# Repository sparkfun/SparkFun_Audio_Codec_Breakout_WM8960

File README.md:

Stereo Audio Codec Breakout - WM8960
========================================

<table class="table table-hover table-striped table-bordered">
  <tr align="center">
   <td></td>
   <td></td>
  </tr>
  <tr align="center">
   <td><i>SparkFun Audio Codec Breakout - WM8960<br />[<a href="https://www.sparkfun.com/products/21250">BOB-21250</a>]</i></td>
   <td><i>SparkFun Audio Codec Breakout - WM8960 with Headers (Qwiic)<br />[<a href="https://www.sparkfun.com/products/21772">BOB-21772</a>]</i></td>
  </tr>
</table>

The SparkFun WM8960 Audio Codec Breakout is a low-power, high-quality stereo codec with 1W Stereo Class D speaker drivers and headphone drivers. The WM8960 acts as a stereo audio ADC and DAC and communicates using I<sup>2</sup>S, a standard audio data protocol (not to be confused with I<sup>2</sup>C). This audio codec is chock full of features some of which include advanced on-chip digital signal processing for automatic level control (ALC) for the line or microphone input, programmable gain amplifier (PGA), pop and click suppression, and its ability to configure I<sup>2</sup>S settings and analog audio path through software via I<sup>2</sup>C. 

The 6x flexible analog input pins allow for a variety of sound source signal types to be routed internally to the ADC inputs. These signal types include line level and microphone level (balanced, and un-balanced) sources. This allows you to accept audio from the sound card on your computer, headphone output of your smartphone, electret microphones, MEMs microphone, etc. The flexible analog signal routing includes PGAs and multiple boost stages so that it can accept a wide range of audio signal levels.

Its efficient class-D driver also means low heat and long battery life when driving 8&ohm; speakers at up to 1W per channel for portable audio applications. As an alternative output, users can also use the audio codec to drive 16&ohm; headphones at up to 40mW for portable audio applications.

Audio feeling a bit... empty? Turn on the 3D enhancement to artificially increase the separation between the left and right channels. In other words, you will feel as if the room is full of sound coming from all directions during playback.  We've written an extensive Arduino Library that allows you to easily control all of the audio codec's features from simple volume control to 3D-enhanced audio playback. 

The board breaks out the WM8960 pins along the edge of the PCB with 0.1"-spaced pins to connect to a breadboard. Utilizing our handy Qwiic system saves you from manually wiring the I<sup>2</sup>C port when configuring the audio codec's settings. A power LED (PWR) is included on the board to indicate when power is applied to the audio CODEC through 3.3V. It can be disabled by cutting the LED jumper on the bottom side. To power the analog (AVDD) and speaker driver (SPKVDD), you will need to include power on the VIN pin. The built-in XC6222 3.3V/700mA voltage regulator regulates the voltage down for the analog circuit. Jumpers for the analog circuit (i..e. AVDD-ISO) and speaker drivers (VIN/SPKVDD) are included for users that want to power each with a separate power supply. 

This board is great for projects that require you to encode or decode audio signals. Add the SparkFun Audio Codec Breakout WM8960 to your next portable digital player or immersive VR game. 

Repository Contents
-------------------

* **/Documents** - Datasheets, additional product information
* **/Hardware** - Eagle design files (.brd, .sch)

Documentation
--------------

* **[Library](https://github.com/sparkfun/SparkFun_WM8960_Arduino_Library)** - Arduino library for the Stereo Audio Codec Breakout - WM8960.
* **[SparkFun Fritzing Part](https://github.com/sparkfun/Fritzing_Parts/blob/main/products/21250_sfe_stereo_audio_codec_breakout_WM8960.fzpz)** - Fritzing diagrams for SparkFun products.
* **[Hookup Guide](https://learn.sparkfun.com/tutorials/2761)** - Basic hookup guide for the Stereo Audio Codec Breakout - WM8960.

Product Versions
----------------

* [BOB-21772](https://www.sparkfun.com/products/21772) - v1.0, with headers
* [BOB-21250](https://www.sparkfun.com/products/21250) - Initial Release, v1.0 

Version History
---------------
* v1.0 - Initial Release 

License Information
-------------------

This product is _**open source**_! 

Please review the LICENSE.md file for license information. 

If you have any questions or concerns on licensing, please contact technical support on our [SparkFun forums](https://forum.sparkfun.com/viewforum.php?f=152).

Distributed as-is; no warranty is given.

- Your friends at SparkFun.

_<COLLABORATION CREDIT>_

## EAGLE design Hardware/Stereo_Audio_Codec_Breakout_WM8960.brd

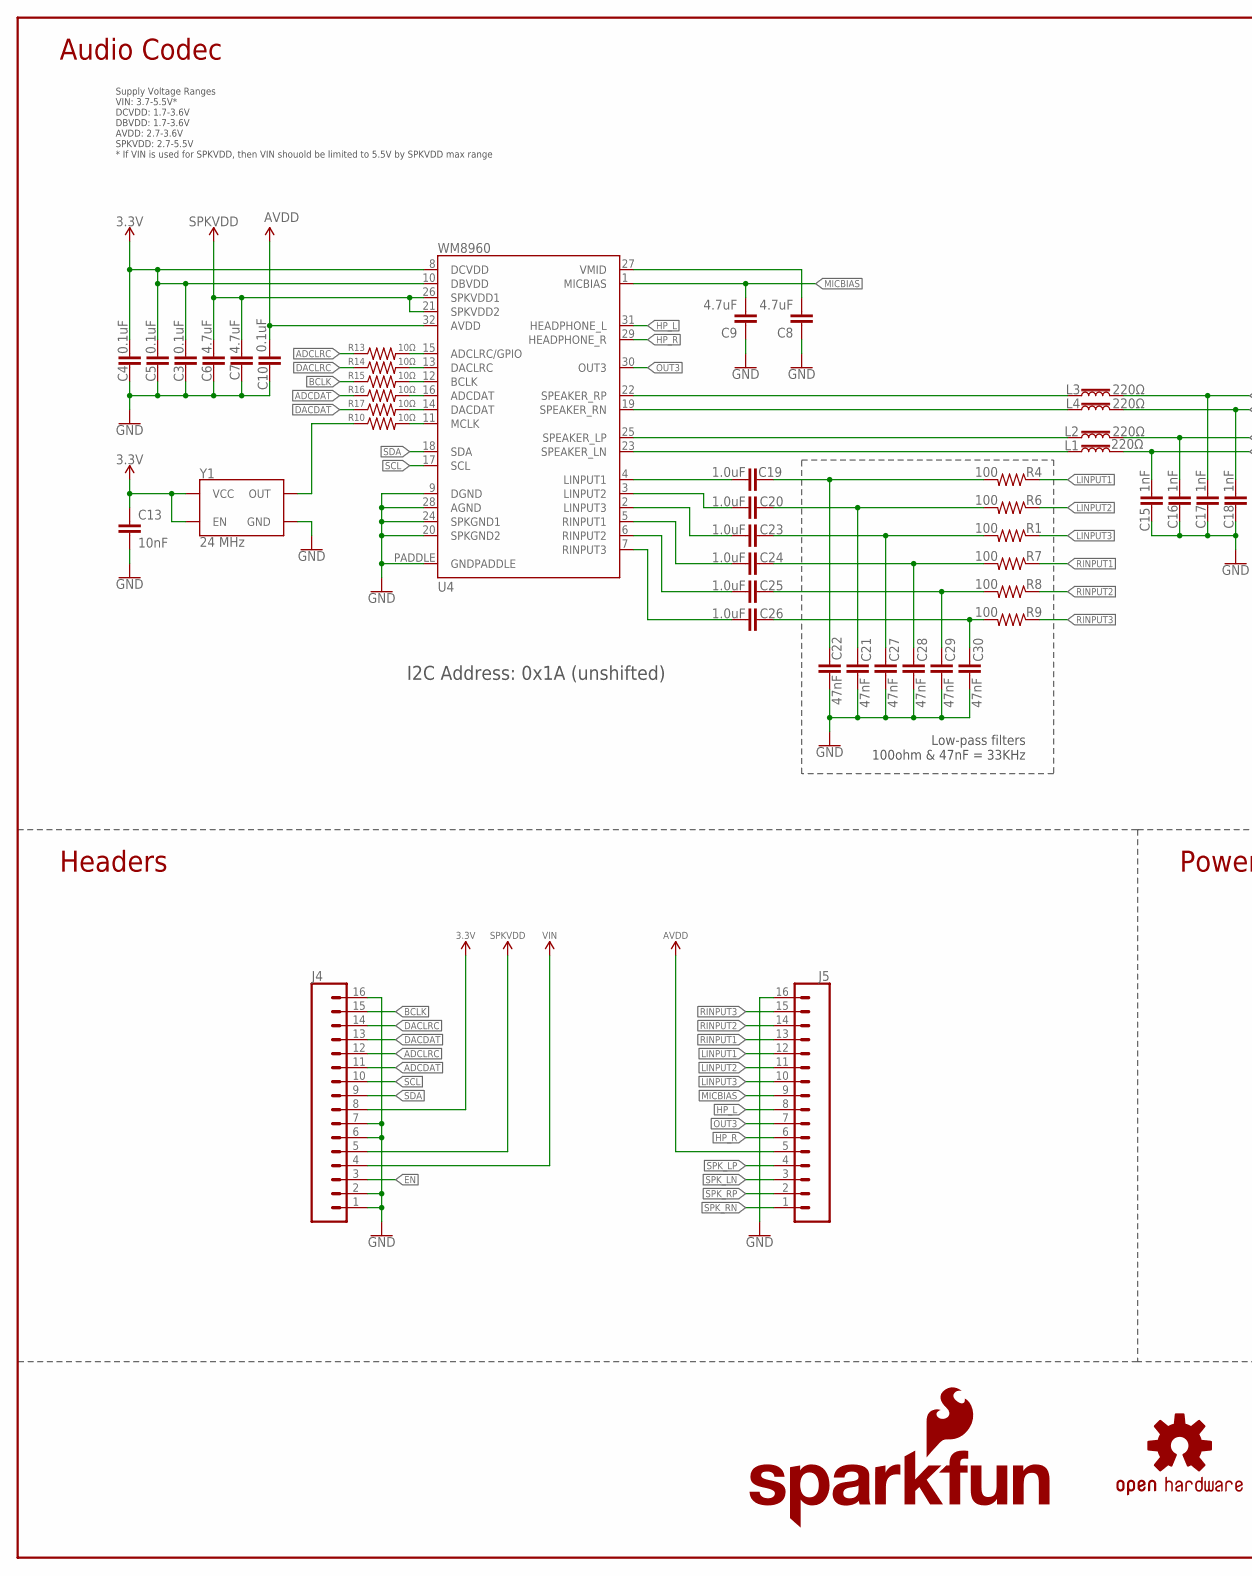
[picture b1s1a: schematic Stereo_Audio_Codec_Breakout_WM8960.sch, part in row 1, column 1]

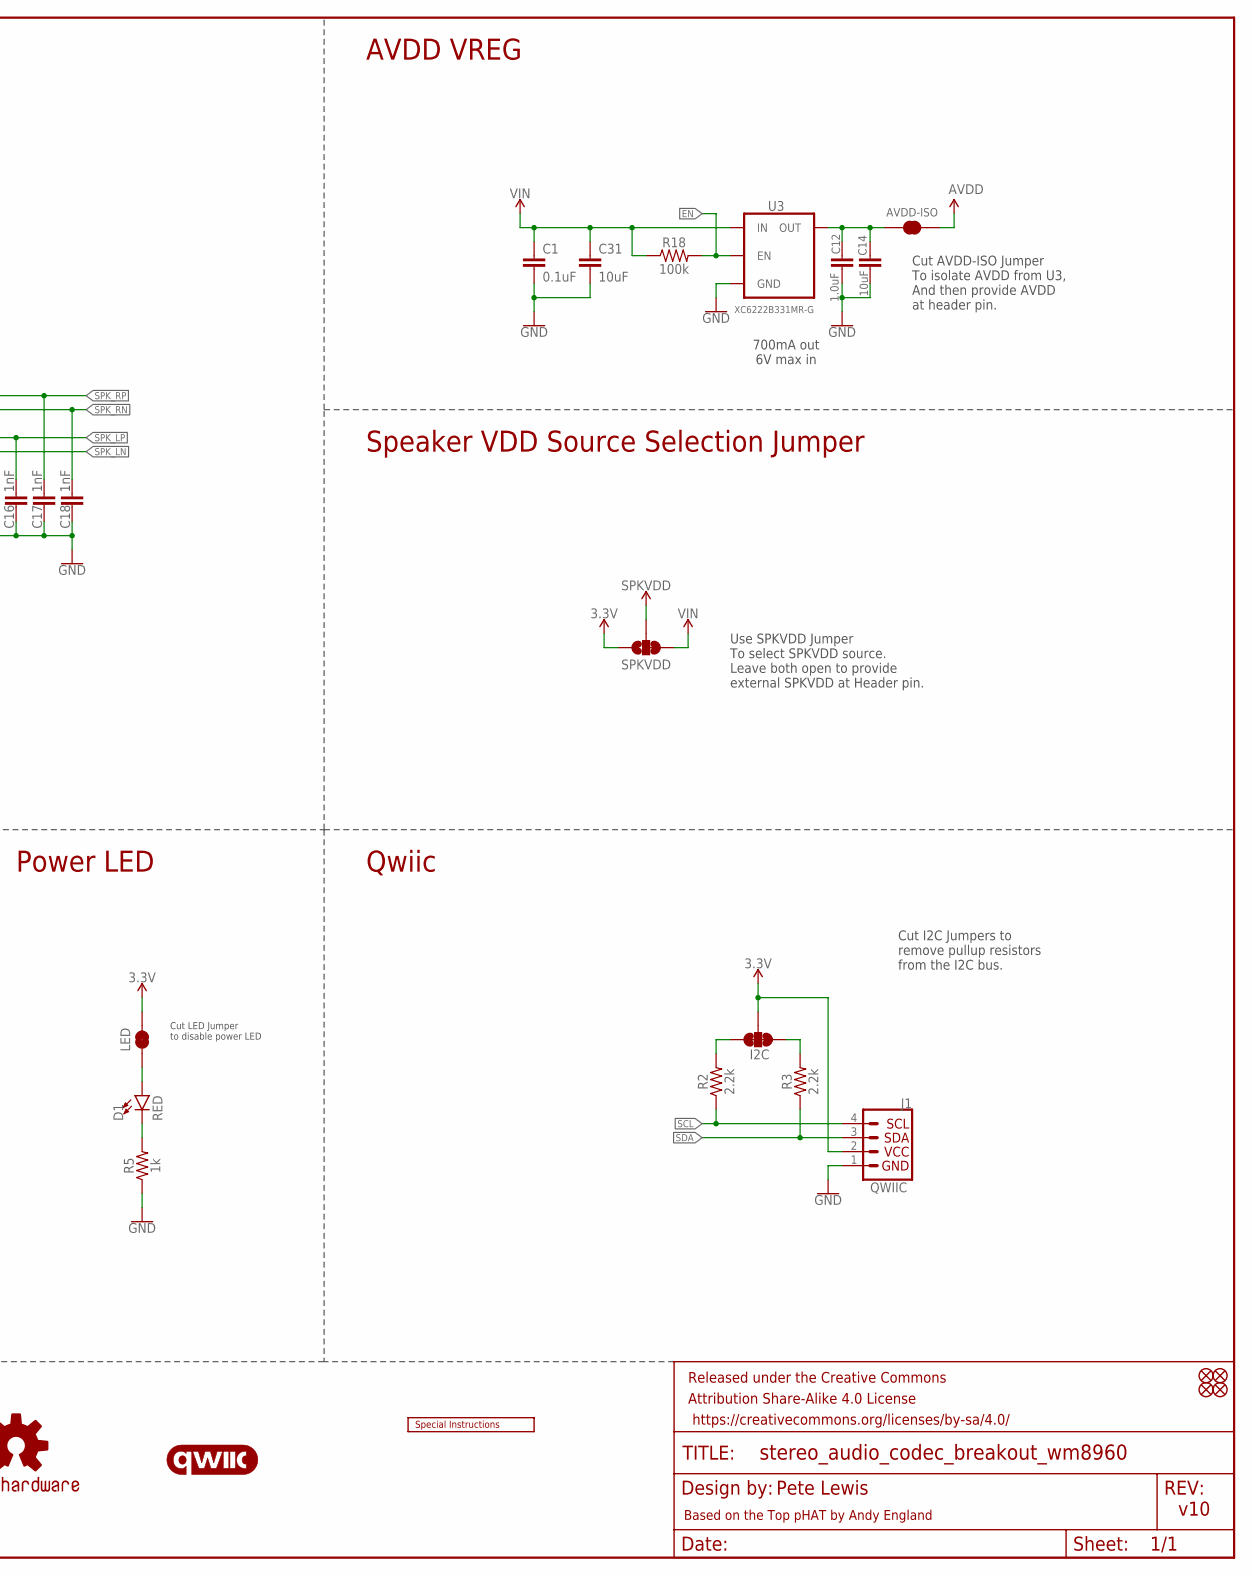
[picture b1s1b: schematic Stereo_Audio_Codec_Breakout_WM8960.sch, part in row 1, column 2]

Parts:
AVDD-ISO: JUMPER-SMT_2_NC_TRACE_SILK; SMT-JUMPER_2_NC_TRACE_SILK
C1, C3, C4, C5, C10: 0.1uF; 0402-TIGHT
C6, C7: 4.7uF; 0603
C8, C9: 4.7uF; 0402-TIGHT
C12, C19, C20, C23, C24, C25, C26: 1.0uF; 0402-TIGHT
C13: 10nF; 0402-TIGHT
C14, C31: 10uF; 0402-TIGHT
C15, C16, C17, C18: 1nF; 0402
C21, C22, C27, C28, C29, C30: 47nF; 0402-TIGHT
D1: RED; LED-0603
FD1, FD2, FD3, FD4: FIDUCIALUFIDUCIAL; FIDUCIAL-MICRO
FRAME1: FRAME-LEDGER; CREATIVE_COMMONS
I2C: JUMPER-SMT_3_2-NC_TRACE_SILK; SMT-JUMPER_3_2-NC_TRACE_SILK
J1: QWIIC; JST04_1MM_RA
J4, J5: CONN_161X16_NO_SILK; 1X16_NO_SILK
L1, L2, L3, L4: 220Ω; 0805
LED: JUMPER-SMT_2_NC_TRACE_SILK; SMT-JUMPER_2_NC_TRACE_SILK
LOGO1: SFE_LOGO_NAME_FLAME.1_INCH; SFE_LOGO_NAME_FLAME_.1
LOGO3: QWIIC_LOGO_4MM; QWIIC_4MM
LOGO4: OSHW-LOGOS; OSHW-LOGO-S
LOGO5: SPECIAL_INSTRUCTIONS-ORDERING; ORDERING_INSTRUCTIONS
R1, R4, R6, R7, R8, R9: 100; 0402-TIGHT
R2, R3: 2.2k; 0402-TIGHT
R5: 1k; 0402-TIGHT
R10, R13, R14, R15, R16, R17: 10Ω; 0402-TIGHT
R18: 100k; 0402-TIGHT
SPKVDD: JUMPER-SMT_3_1-NC_TRACE_SILK; SMT-JUMPER_3_1-NC_TRACE_SILK
U3: XC6222B331MR-G; SOT23-5
U4: WM8960; QFN-32
Y1: 24 MHz; RESONATOR-SMD-3.2X2.5

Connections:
3.3V: C3.2, C4.2, C5.2, C13.1, I2C.2, J1.2, J4.8, LED.2, SPKVDD.1, U4.8 (DCVDD), U4.10 (DBVDD), Y1.1 (EN), Y1.4 (VCC)
ADCDAT: J4.11, R16.1
ADCLRC: J4.12, R13.1
AVDD: AVDD-ISO.2, C10.2, J5.5, U4.32 (AVDD)
AVDD-REG: AVDD-ISO.1, C12.1, C14.1, U3.5 (OUT)
BCLK: J4.15, R15.1
DACDAT: J4.13, R17.1
DACLRC: J4.14, R14.1
EN: J4.3, R18.2, U3.3 (EN)
GND: C1.2, C3.1, C4.1, C5.1, C6.2, C7.2, C8.1, C9.1, C10.1, C12.2, C13.2, C14.2, C15.2, C16.2, C17.2, C18.2, C21.2, C22.2, C27.2, C28.2, C29.2, C30.2, C31.2, J1.1, J4.1, J4.2, J4.6, J4.7, J4.16, J5.16, R5.1, U3.2 (GND), U4.9 (DGND), U4.20 (SPKGND2), U4.24 (SPKGND1), U4.28 (AGND), U4.PADDLE (GNDPADDLE), Y1.2 (GND)
HP_L: J5.8, U4.31 (HEADPHONE_L)
HP_R: J5.6, U4.29 (HEADPHONE_R)
LINPUT1: J5.12, R4.1
LINPUT2: J5.11, R6.1
LINPUT3: J5.10, R1.1
MICBIAS: C9.2, J5.9, U4.1 (MICBIAS)
unnamed: L3.1, U4.22 (SPEAKER_RP)
unnamed: R13.2, U4.15 (ADCLRC/GPIO)
unnamed: L4.1, U4.19 (SPEAKER_RN)
unnamed: L2.1, U4.25 (SPEAKER_LP)
unnamed: L1.1, U4.23 (SPEAKER_LN)
unnamed: D1.C, R5.2
unnamed: D1.A, LED.1
unnamed: C26.2, U4.7 (RINPUT3)
unnamed: C25.2, U4.6 (RINPUT2)
unnamed: C23.2, U4.2 (LINPUT3)
unnamed: R10.1, Y1.3 (OUT)
unnamed: C20.2, U4.3 (LINPUT2)
unnamed: C20.1, C21.1, R6.2
unnamed: C19.1, C22.1, R4.2
unnamed: C23.1, C27.1, R1.2
unnamed: I2C.3, R2.2
unnamed: I2C.1, R3.2
unnamed: C24.1, C28.1, R7.2
unnamed: C25.1, C29.1, R8.2
unnamed: C26.1, C30.1, R9.2
unnamed: R14.2, U4.13 (DACLRC)
unnamed: R15.2, U4.12 (BCLK)
unnamed: R16.2, U4.16 (ADCDAT)
unnamed: R17.2, U4.14 (DACDAT)
unnamed: R10.2, U4.11 (MCLK)
unnamed: C19.2, U4.4 (LINPUT1)
unnamed: C24.2, U4.5 (RINPUT1)
unnamed: C8.2, U4.27 (VMID)
OUT3: J5.7, U4.30 (OUT3)
RINPUT1: J5.13, R7.1
RINPUT2: J5.14, R8.1
RINPUT3: J5.15, R9.1
SCL: J1.4, J4.10, R2.1, U4.17 (SCL)
SDA: J1.3, J4.9, R3.1, U4.18 (SDA)
SPKVDD: C6.1, C7.1, J4.5, SPKVDD.2, U4.21 (SPKVDD2), U4.26 (SPKVDD1)
SPK_LN: C15.1, J5.3, L1.2
SPK_LP: C16.1, J5.4, L2.2
SPK_RN: C18.1, J5.1, L4.2
SPK_RP: C17.1, J5.2, L3.2
VIN: C1.1, C31.1, J4.4, R18.1, SPKVDD.3, U3.1 (IN)

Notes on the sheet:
Pete Lewis
Audio Codec
Cut I2C Jumpers to remove pullup resistors from the I2C bus.
v10
Based on the Top pHAT by Andy England
I2C Address: 0x1A (unshifted)
Cut LED Jumper to disable power LED
Low-pass filters 100ohm & 47nF = 33KHz
Supply Voltage Ranges VIN: 3.7-5.5V* DCVDD: 1.7-3.6V DBVDD: 1.7-3.6V AVDD: 2.7-3.6V SPKVDD: 2.7-5.5V * If VIN is used for SPKVDD, then VIN shouold be limited to 5.5V by SPKVDD max range
AVDD VREG
Headers
Qwiic
Speaker VDD Source Selection Jumper
700mA out 6V max in
Cut AVDD-ISO Jumper To isolate AVDD from U3, And then provide AVDD at header pin.
Use SPKVDD Jumper To select SPKVDD source. Leave both open to provide external SPKVDD at Header pin.
Power LED

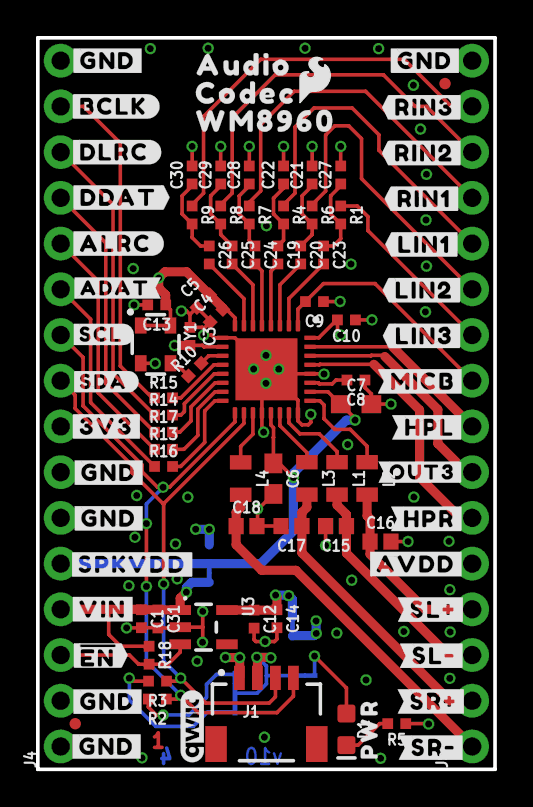
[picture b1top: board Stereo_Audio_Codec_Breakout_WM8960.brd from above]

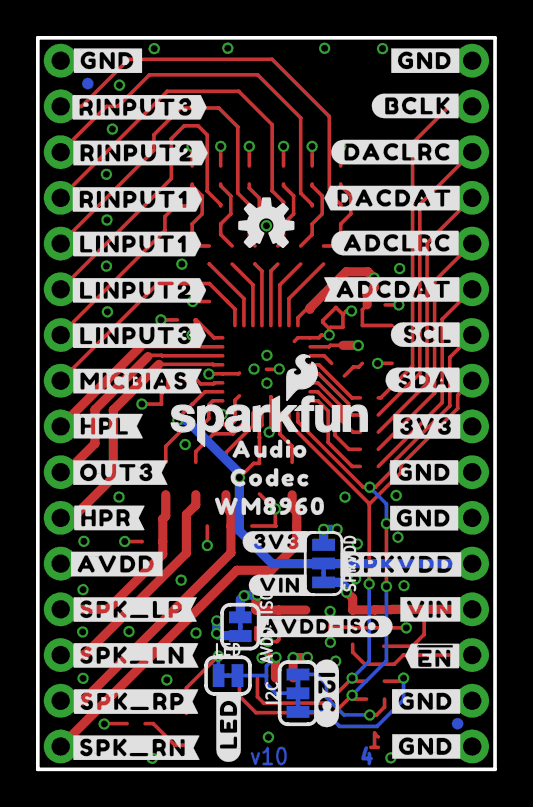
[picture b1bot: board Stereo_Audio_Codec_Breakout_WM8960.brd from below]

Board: 4 copper layers, 25.4 x 40.6 mm, 146 parts (48 on the bottom side), 56 nets.

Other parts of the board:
U$1: AUDIO8960896055
U$2: CODEC8960896056
U$3: CODEC8960896057
U$4, U$7, U$8, U$9, U$11, U$12, U$17, U$18, U$19, U$31, U$32, U$50: #GND#8
U$5: #BCLK#0
U$10, U$48: #AVDD#22
U$13: #SR##4
U$14: #SL##6
U$15: #SR##5
U$16: #SL##7
U$20: #AVDD#ISO#0
U$21: #3V3#0
U$22: #VIN#0
U$23: #ALRC#0
U$24: #DLRC#1
U$26: #HPL#10
U$27: #HPR#11
U$28, U$51: #3V3#12
U$29: SFE_LOGO_FLAME_.1
U$30, U$64: #SPKVDD#51
U$34: ##EN##1
U$35: PWR12
U$36: WM8960896054
U$37: #OUT3#0
U$38: ##EN##2
U$39: #LED#17
U$40: #I2C#18
U$41: #OUT3#4
U$44: #RINPUT1#0
U$45, U$46: #VIN#19
U$47: #RINPUT2#0
U$49: #RINPUT3#0
U$52: #ADCLRC#2
U$54: #RIN3#0
U$55: #DACLRC#4
U$56: #RIN2#0
U$57: #BCLK#5
U$58: #ADCDAT#6
U$59: #MICB#31
U$60: WM89600
U$61: AUDIO0
U$62: #LINPUT1#0
U$63: #LINPUT2#0
U$65: #LINPUT3#0
U$66: #SCL#0
U$67: #SDA#0
U$68: #RIN1#0
U$69: #DDAT#9
U$70: #DACDAT#8
U$71: #ADAT#10
U$74: #SCL#40
U$75: #SDA#41
U$76: #LIN1#0
U$77: #LIN2#0
U$78: #LIN3#0
U$79: #MICBIAS#42
U$80: #HPL#43
U$82: #HPR#45
U$83: #SPK_LP#46
U$84: #SPK_LN#47
U$85: #SPK_RP#48
U$86: #SPK_RN#49

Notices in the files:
parts and their libraries:
SparkFun-Connectors: Licensing: Creative Commons ShareAlike 4.0 International - https://creativecommons.org/licenses/by-sa/4.0
SparkFun-Aesthetics: Released under the Creative Commons Attribution Share-Alike 4.0 License
SparkFun-Aesthetics: https://creativecommons.org/licenses/by-sa/4.0
